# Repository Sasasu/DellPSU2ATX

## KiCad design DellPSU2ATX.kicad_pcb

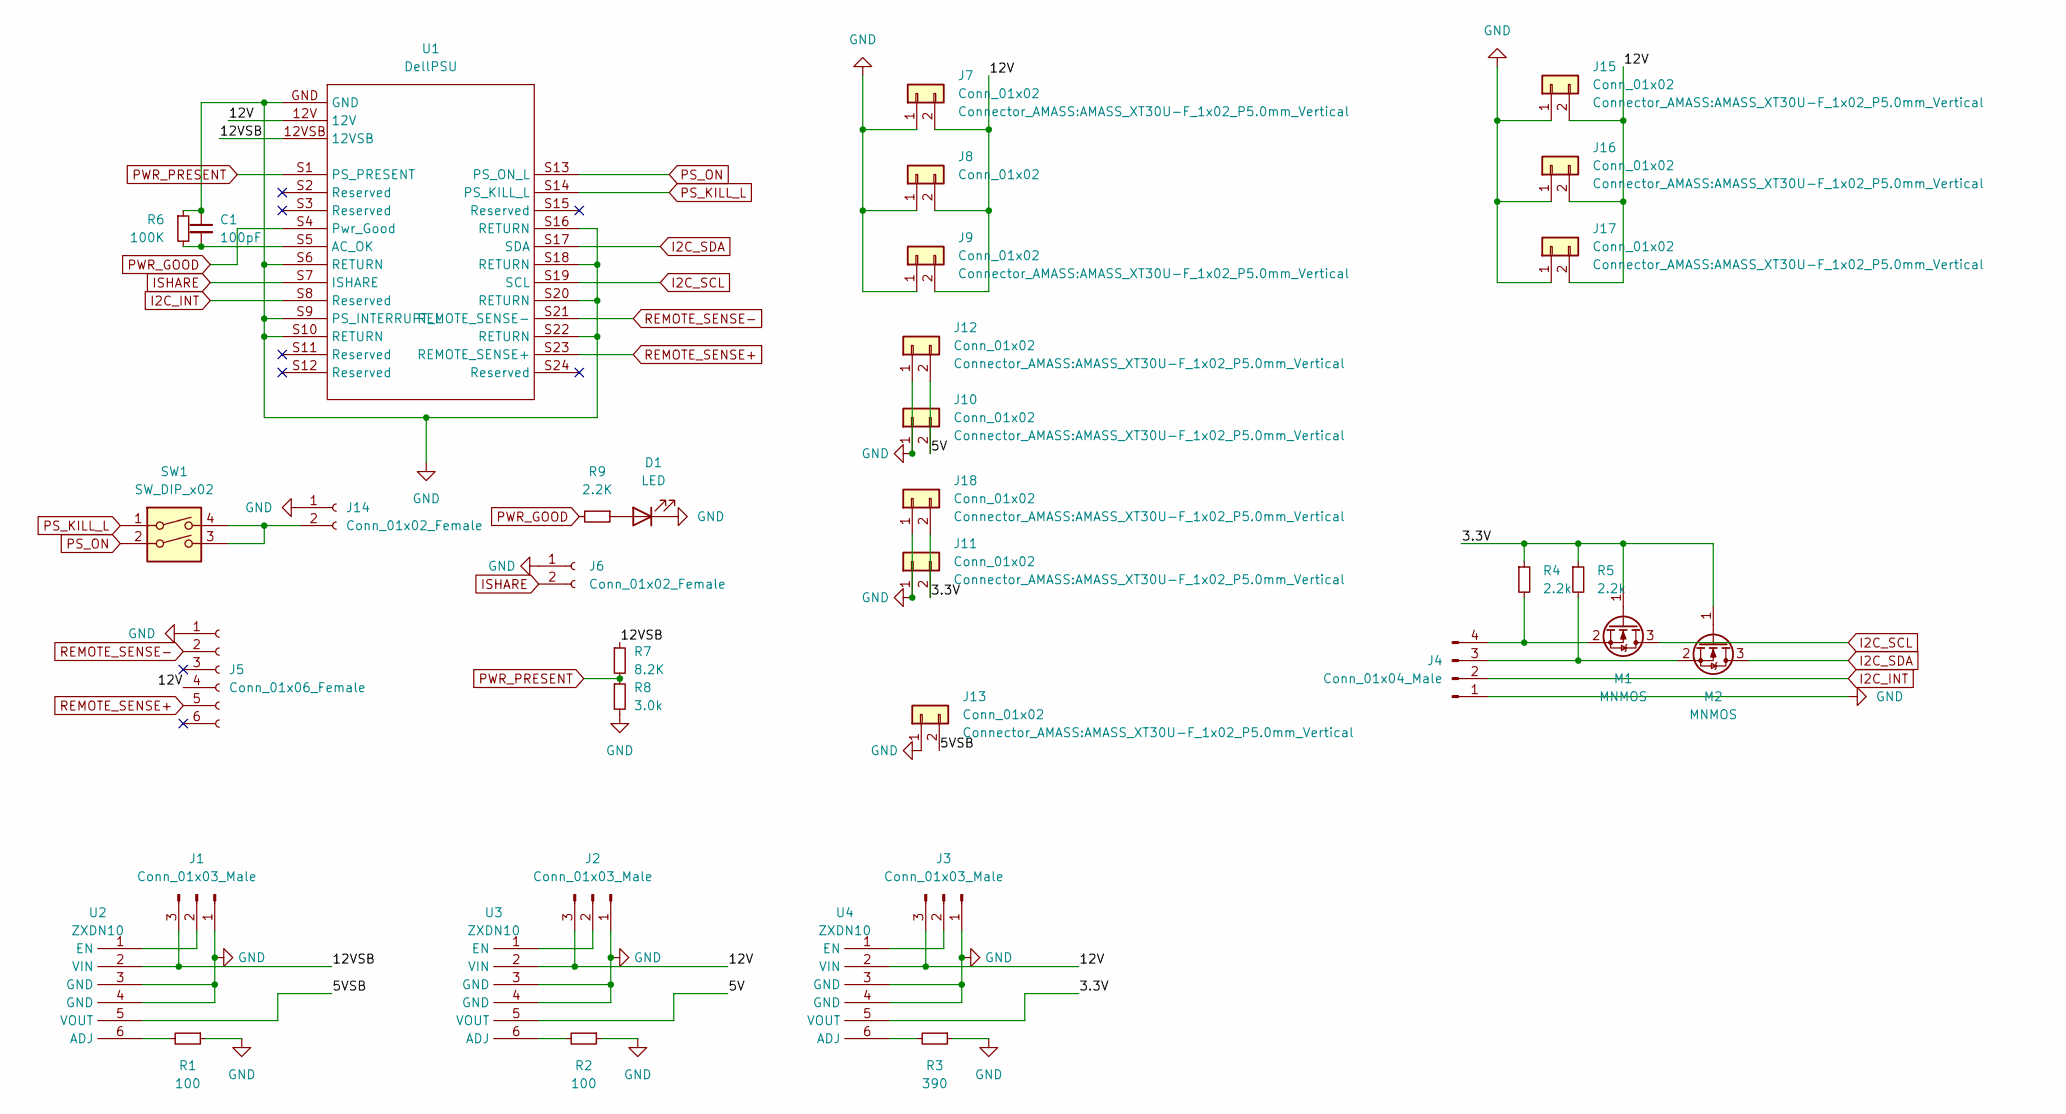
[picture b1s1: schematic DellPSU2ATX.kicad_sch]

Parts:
C1: 100pF; C_0402_1005Metric_Pad0.74x0.62mm_HandSolder
D1: LED; LED_0402_1005Metric_Pad0.77x0.64mm_HandSolder
J1, J2, J3: Conn_01x03_Male; PinHeader_1x03_P2.54mm_Vertical
J4: Conn_01x04_Male; PinHeader_1x04_P2.54mm_Vertical
J5: Conn_01x06_Female; PinHeader_1x06_P2.54mm_Vertical
J6, J14: Conn_01x02_Female; PinHeader_1x02_P2.54mm_Vertical
J7, J8, J9, J10, J11, J12, J13, J15, J16, J17, J18: Conn_01x02; AMASS_XT30U-F_1x02_P5.0mm_Vertical
M1, M2: MNMOS; SOT-23
R1, R2: 100; R_0402_1005Metric_Pad0.72x0.64mm_HandSolder
R3: 390; R_0402_1005Metric_Pad0.72x0.64mm_HandSolder
R4, R5: 2.2k; R_0402_1005Metric_Pad0.72x0.64mm_HandSolder
R6: 100K; R_0402_1005Metric_Pad0.72x0.64mm_HandSolder
R7: 8.2K; R_0402_1005Metric_Pad0.72x0.64mm_HandSolder
R8: 3.0k; R_0402_1005Metric_Pad0.72x0.64mm_HandSolder
R9: 2.2K; R_0402_1005Metric_Pad0.72x0.64mm_HandSolder
SW1: SW_DIP_x02; SW_DIP_SPSTx02_Slide_9.78x7.26mm_W8.61mm_P2.54mm
U1: DellPSU
U2, U3, U4: ZXDN10

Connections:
/3.3V: J11.2, J18.2, M1.1 (G), M2.1 (G), R4.1, R5.1, U4.5 (VOUT)
/5V: J10.2, J12.2, U3.5 (VOUT)
/5VSB: J13.2, U2.5 (VOUT)
/12V: J2.3, J3.3, J5.4, J7.2, J8.2, J9.2, J15.2, J16.2, J17.2, U1.12V, U3.2 (VIN), U4.2 (VIN)
/12VSB: J1.3, R7.1, U1.12VSB, U2.2 (VIN)
GND: C1.1, D1.1 (K), J1.1, J2.1, J3.1, J4.1, J5.1, J6.1, J7.1, J8.1, J9.1, J10.1, J11.1, J12.1, J13.1, J14.1, J15.1, J16.1, J17.1, J18.1, R1.1, R2.1, R3.1, R6.1, R8.2, U1.GND, U1.S6 (RETURN), U1.S9 (PS_INTERRUPT_L), U1.S10 (RETURN), U1.S16 (RETURN), U1.S18 (RETURN), U1.S20 (RETURN), U1.S22 (RETURN), U2.3 (GND), U2.4 (GND), U3.3 (GND), U3.4 (GND), U4.3 (GND), U4.4 (GND)
I2C_INT: J4.2, U1.S8 (Reserved)
I2C_SCL: M1.3 (D), U1.S19 (SCL)
I2C_SDA: M2.3 (D), U1.S17 (SDA)
ISHARE: J6.2, U1.S7 (ISHARE)
unnamed: C1.2, R6.2, U1.S5 (AC_OK)
unnamed: D1.2 (A), R9.1
unnamed: J1.2, U2.1 (EN)
unnamed: J2.2, U3.1 (EN)
unnamed: J3.2, U4.1 (EN)
unnamed: J4.3, M2.2 (S), R5.2
unnamed: J4.4, M1.2 (S), R4.2
unnamed: J14.2, SW1.3, SW1.4
unnamed: R1.2, U2.6 (ADJ)
unnamed: R2.2, U3.6 (ADJ)
unnamed: R3.2, U4.6 (ADJ)
PS_KILL_L: SW1.1, U1.S14 (PS_KILL_L)
PS_ON: SW1.2, U1.S13 (PS_ON_L)
PWR_GOOD: R9.2, U1.S4 (Pwr_Good)
PWR_PRESENT: R7.2, R8.1, U1.S1 (PS_PRESENT)
REMOTE_SENSE+: J5.5, U1.S23 (REMOTE_SENSE+)
REMOTE_SENSE-: J5.2, U1.S21 (REMOTE_SENSE-)

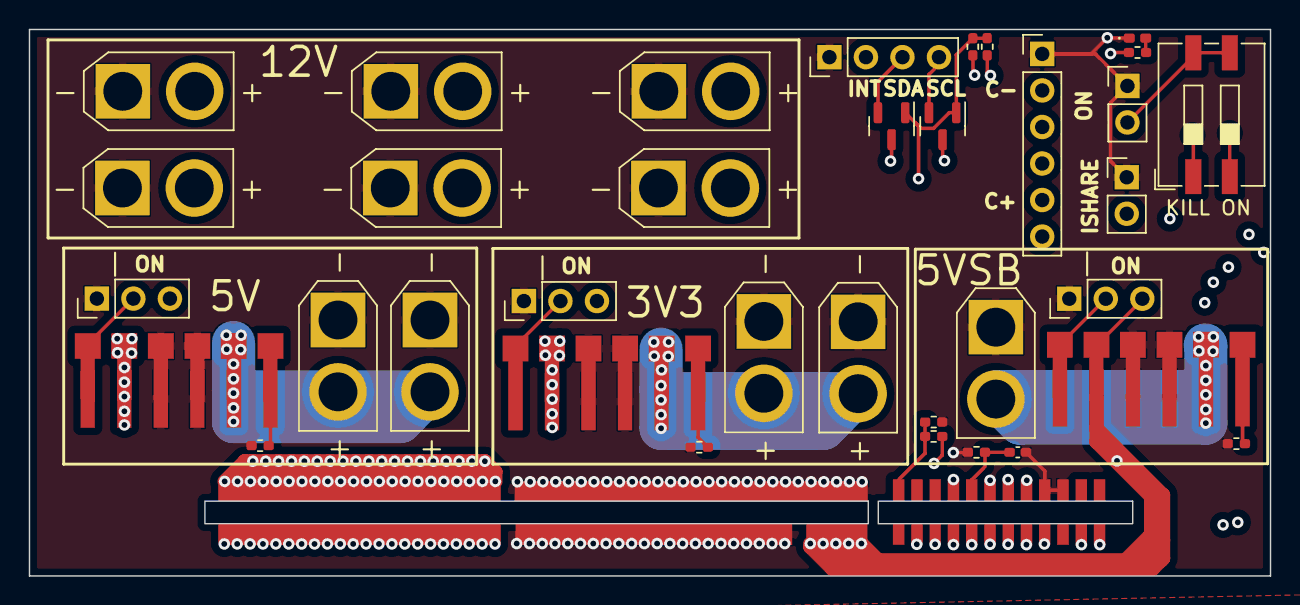
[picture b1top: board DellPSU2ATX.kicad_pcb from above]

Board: 4 copper layers, 86.3 x 38.0 mm, 36 parts (0 on the bottom side), 27 nets.

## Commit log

2022-11-06 add readme
